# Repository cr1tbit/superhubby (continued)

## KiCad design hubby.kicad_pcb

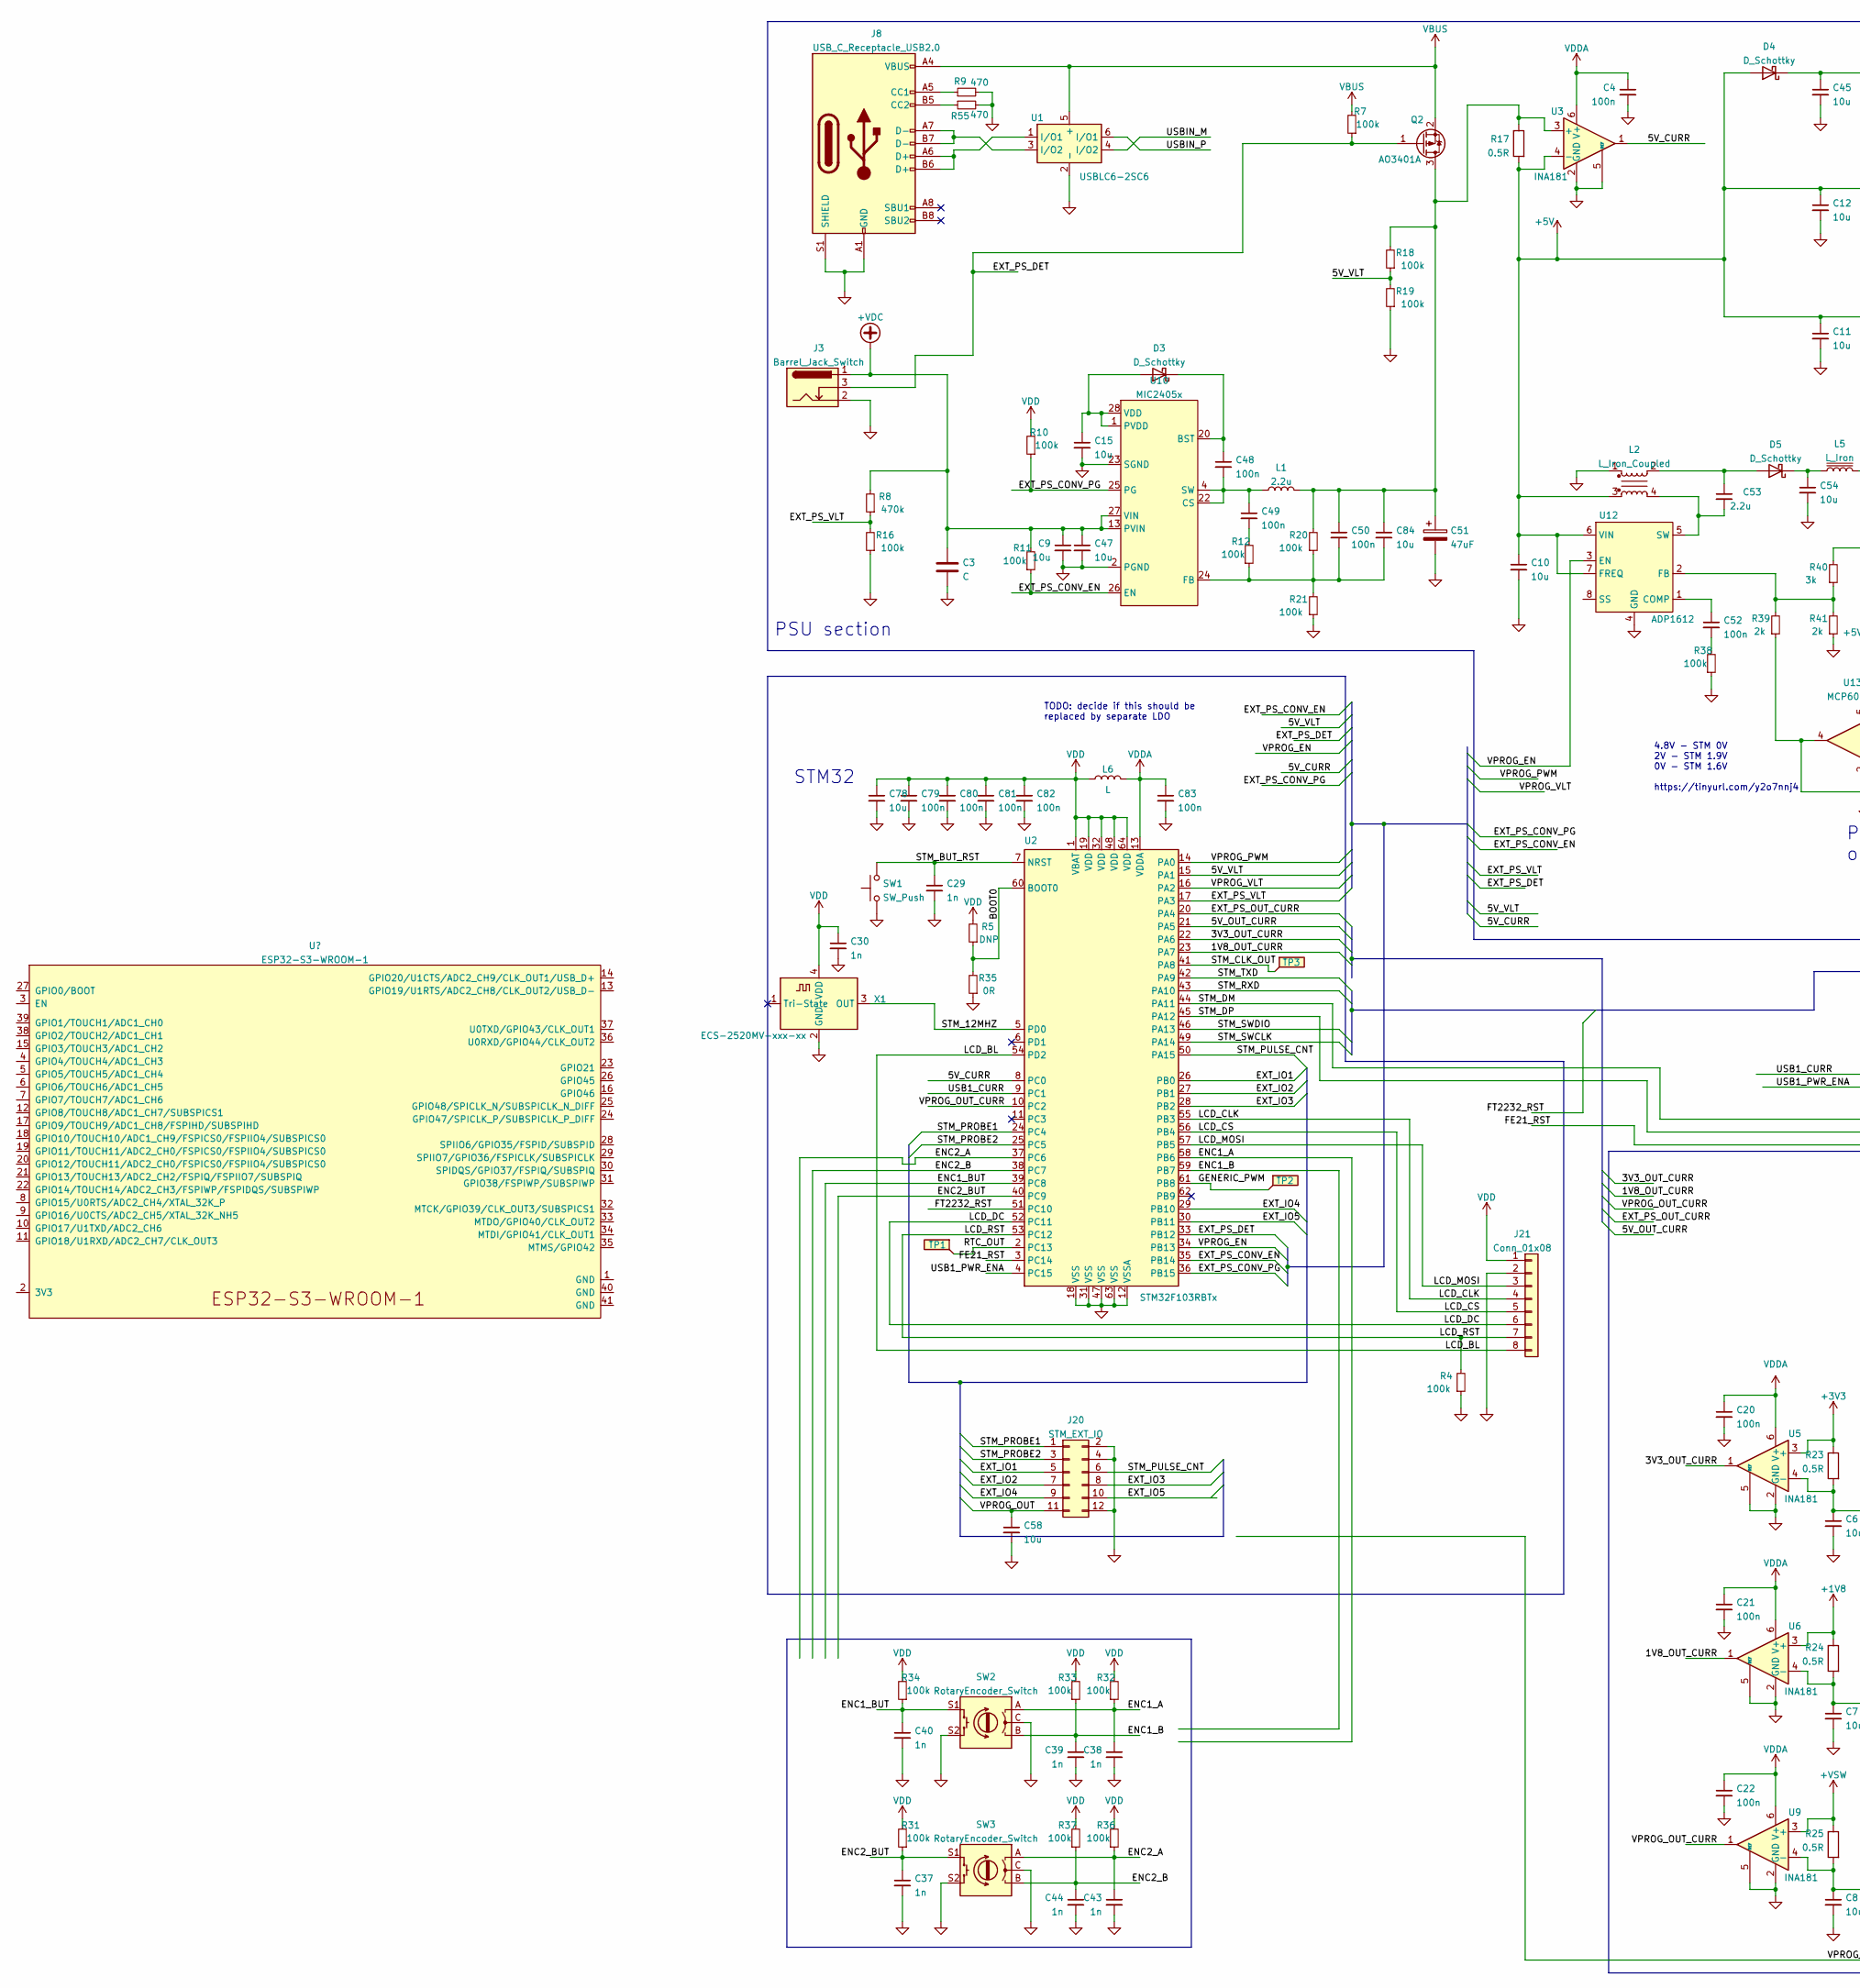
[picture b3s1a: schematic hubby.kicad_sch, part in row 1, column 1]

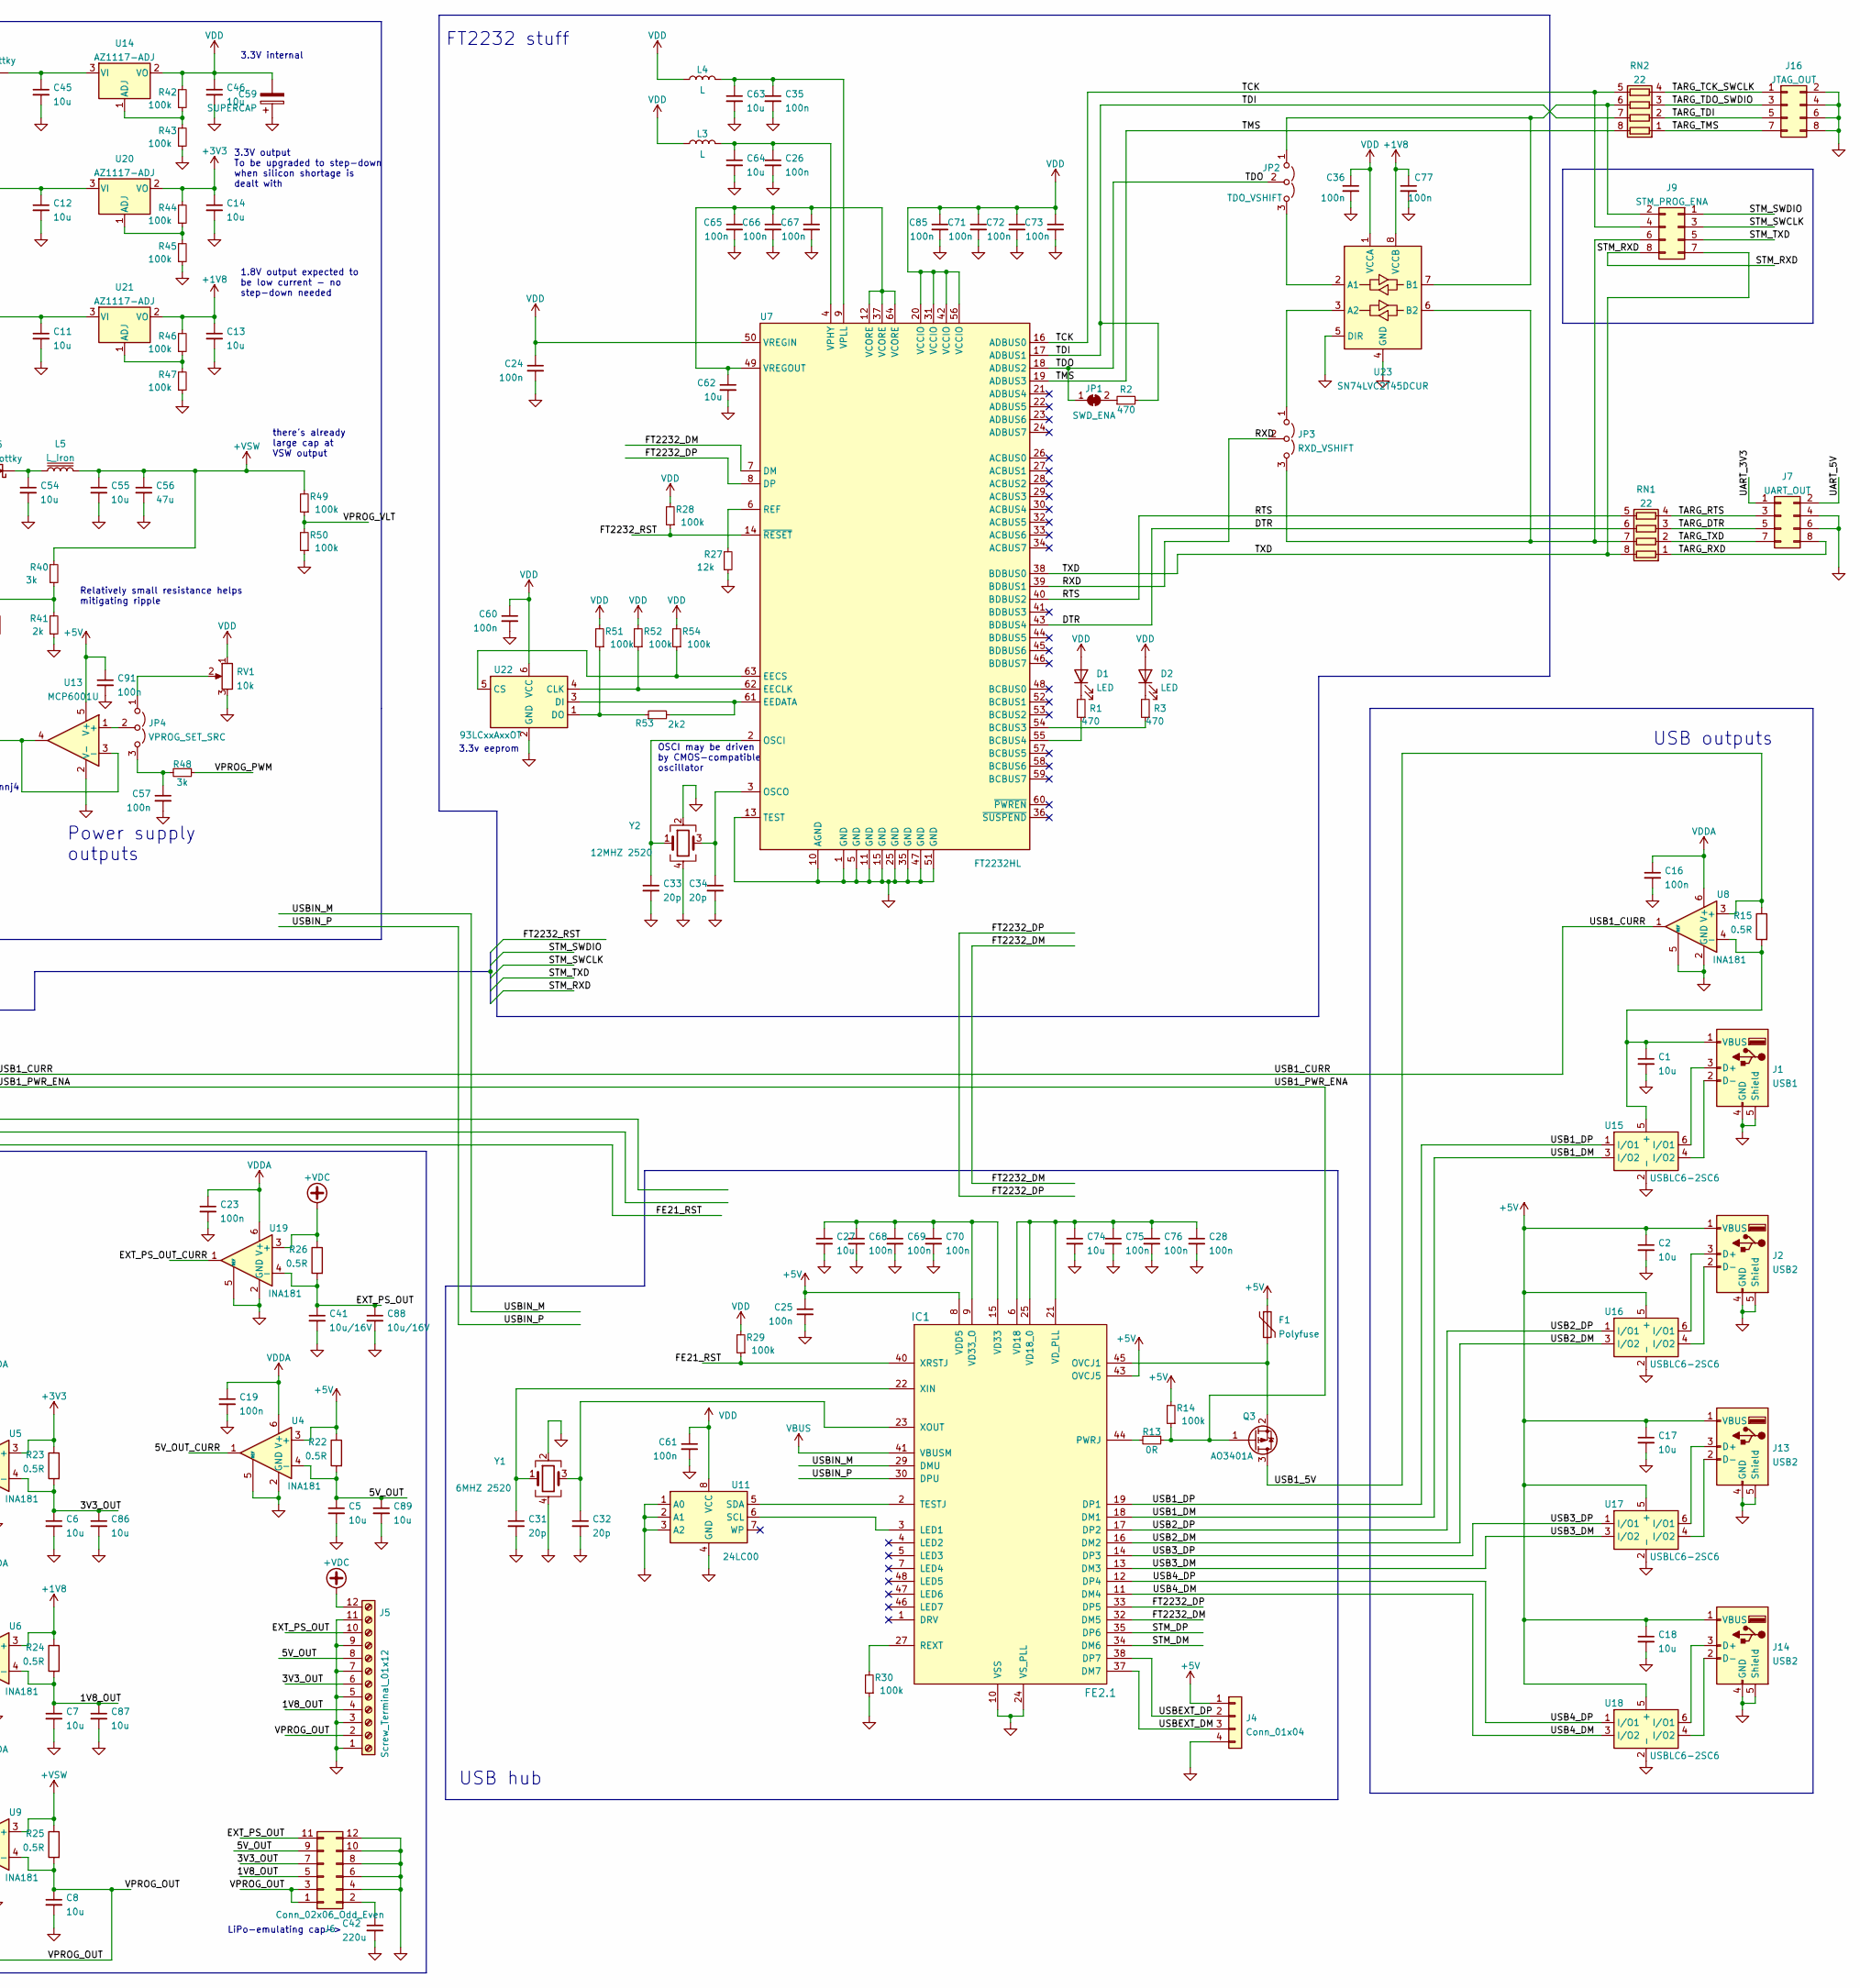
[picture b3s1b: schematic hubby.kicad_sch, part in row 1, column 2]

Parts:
C1, C2, C5, C6, C7, C8, C9, C10, C11, C12, C13, C14, C15, C17, C18, C27, C45, C46, C47, C54, C55, C58, C62, C63, C64, C74, C78, C84, C86, C87, C89: 10u; C_0805_2012Metric
C3: C; CP_Radial_D5.0mm_P2.50mm
C4, C16, C19, C20, C21, C22, C23, C24, C25, C26, C28, C35, C36, C48, C49, C50, C52, C57, C60, C61, C65, C66, C67, C68, C69, C70, C71, C72, C73, C75, C76, C77, C79, C80, C81, C82, C83, C85, C91: 100n; C_0402_1005Metric
C29, C30, C37, C38, C39, C40, C43, C44: 1n; C_0402_1005Metric
C31, C32, C33, C34: 20p; C_0402_1005Metric
C41, C88: 10u/16V; C_0805_2012Metric
C42: 220u; CP_Radial_D5.0mm_P2.50mm
C51: 47uF; CP_Radial_D5.0mm_P2.50mm
C53: 2.2u; C_0805_2012Metric
C56: 47u; C_0805_2012Metric
C59: SUPERCAP; CP_Radial_D5.0mm_P2.50mm
D1, D2: LED; LED_0805_2012Metric_Pad1.15x1.40mm_HandSolder
D3, D4, D5: D_Schottky; D_SMA
F1: Polyfuse; R_1206_3216Metric_Pad1.30x1.75mm_HandSolder
IC1: FE2.1; LQFP-48_7x7mm_P0.5mm
J1: USB1; USB_A_Molex_67643_Horizontal
J2, J13, J14: USB2; USB_A_Molex_67643_Horizontal
J3: Barrel_Jack_Switch; BarrelJack_CUI_PJ-102AH_Horizontal
J4: Conn_01x04; PinHeader_1x04_P2.00mm_Vertical
J5: Screw_Terminal_01x12; TerminalBlock_Phoenix_PT-1,5-12-5.0-H_1x12_P5.00mm_Horizont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
J6: Conn_02x06_Odd_Even; PinHeader_2x06_P2.54mm_Horizontal
J7: UART_OUT; PinHeader_2x04_P2.54mm_Horizontal
J8: USB_C_Receptacle_USB2.0; USB_C_Receptacle_GCT_USB4085
J9: STM_PROG_ENA; PinHeader_2x04_P2.54mm_Vertical
J16: JTAG_OUT; PinHeader_2x04_P2.54mm_Horizontal
J20: STM_EXT_IO; PinHeader_2x06_P2.54mm_Horizontal
J21: Conn_01x08; PinSocket_1x08_P2.54mm_Vertical
JP1: SWD_ENA; SolderJumper-2_P1.3mm_Bridged2Bar_RoundedPad1.0x1.5mm
JP2: TDO_VSHIFT; PinHeader_1x03_P2.54mm_Vertical
JP3: RXD_VSHIFT; PinHeader_1x03_P2.54mm_Vertical
JP4: VPROG_SET_SRC; PinHeader_1x03_P2.54mm_Vertical
L1: 2.2u; L_Vishay_IHLP-4040
L2: L_Iron_Coupled; L_Wuerth_WE-DD-Typ-M-Typ-S
L3, L4, L6: L; L_1206_3216Metric_Pad1.22x1.90mm_HandSolder
L5: L_Iron; L_1206_3216Metric_Pad1.42x1.75mm_HandSolder
Q2, Q3: AO3401A; SOT-23
R1, R2, R3, R9, R55: 470; R_0603_1608Metric_Pad0.98x0.95mm_HandSolder
R4, R7, R10, R11, R12, R14, R16, R18, R19, R20, R21, R28, R29, R30, R31, R32, R33, R34, R36, R37, R38, R42, R43, R44, R45, R46, R47, R49, R50, R51, R52, R54: 100k; R_0603_1608Metric_Pad0.98x0.95mm_HandSolder
R5: DNP; R_0603_1608Metric_Pad0.98x0.95mm_HandSolder
R8: 470k; R_0603_1608Metric_Pad0.98x0.95mm_HandSolder
R13, R35: 0R; R_0603_1608Metric_Pad0.98x0.95mm_HandSolder
R15, R17, R22, R23, R24, R25, R26: 0.5R; R_1206_3216Metric_Pad1.30x1.75mm_HandSolder
R27: 12k; R_0603_1608Metric_Pad0.98x0.95mm_HandSolder
R39, R41: 2k; R_0603_1608Metric_Pad0.98x0.95mm_HandSolder
R40, R48: 3k; R_0603_1608Metric_Pad0.98x0.95mm_HandSolder
R53: 2k2; R_0603_1608Metric_Pad0.98x0.95mm_HandSolder
RN1, RN2: 22; R_Array_Convex_4x0603
RV1: 10k; Potentiometer_Runtron_RM-065_Vertical
SW1: SW_Push; SW_PUSH_6mm_H4.3mm
SW2, SW3: RotaryEncoder_Switch; RotaryEncoder_Alps_EC12E-Switch_Vertical_H20mm_CircularMoun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
TP1: RTC_OUT; TestPoint_Pad_D1.0mm
TP2: GENERIC_PWM; TestPoint_Pad_D1.0mm
TP3: STM_CLK_OUT; TestPoint_Pad_D1.0mm
U1, U15, U16, U17, U18: USBLC6-2SC6; SOT-23-6
U2: STM32F103RBTx; LQFP-64_10x10mm_P0.5mm
U3, U4, U5, U6, U8, U9, U19: INA181; SOT-23-6
U7: FT2232HL; LQFP-64_10x10mm_P0.5mm
U10: MIC2405x; QFN-28-3EP_5x6mm_MIC2045x
U11: 24LC00; SOIC-8_3.9x4.9mm_P1.27mm
U12: ADP1612; MSOP-8_3x3mm_P0.65mm
U13: MCP6001U; SOT-23-5
U14, U20, U21: AZ1117-ADJ; SOT-223-3_TabPin2
U22: 93LCxxAxxOT; SOT-23-6
U23: SN74LVC2T45DCUR; VSSOP-8_2.4x2.1mm_P0.5mm
X1: ECS-2520MV-xxx-xx; Oscillator_SMD_ECS_2520MV-xxx-xx-4Pin_2.5x2.0mm
Y1: 6MHZ 2520; Crystal_SMD_2520-4Pin_2.5x2.0mm
Y2: 12MHZ 2520; Crystal_SMD_2520-4Pin_2.5x2.0mm

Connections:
+1V8: C13.1, C77.1, R24.1, R46.2, U6.3 (+), U21.2 (VO), U23.8 (VCCB)
+3V3: C14.1, R23.1, R44.2, U5.3 (+), U20.2 (VO)
+5V: C2.1, C10.1, C11.1, C12.1, C17.1, C18.1, C25.1, C91.1, D4.2 (A), F1.1, IC1.8 (VDD5), IC1.43 (OVCJ5), J2.1 (VBUS), J4.1, J13.1 (VBUS), J14.1 (VBUS), L2.3, R14.2, R17.2, R22.1, U3.4 (-), U4.3 (+), U12.6 (VIN), U12.7 (FREQ), U13.5 (V+), U16.5 (+), U17.5 (+), U18.5 (+), U20.3 (VI), U21.3 (VI)
+VDC: C3.1, C9.1, C47.1, J3.1, J5.12, R8.2, R11.2, R26.1, U10.13 (PVIN), U10.14 (PVIN), U10.15 (PVIN), U10.16 (PVIN), U10.17 (PVIN), U10.18 (PVIN), U10.19 (PVIN), U10.27 (VIN), U19.3 (+)
+VSW: C55.1, C56.1, L5.2, R25.1, R40.2, R49.2, U9.3 (+)
/1V8_OUT: C7.1, C87.1, J5.4, J6.5, R24.2, U6.4 (-)
/1V8_OUT_CURR: U2.23 (PA7), U6.1
/3V3_OUT: C6.1, C86.1, J5.6, J6.7, R23.2, U5.4 (-)
/3V3_OUT_CURR: U2.22 (PA6), U5.1
/5V_CURR: U2.8 (PC0), U3.1
/5V_OUT: C5.1, C89.1, J5.8, J6.9, R22.2, U4.4 (-)
/5V_OUT_CURR: U2.21 (PA5), U4.1
/5V_VLT: R18.1, R19.2, U2.15 (PA1)
/BOOT0: R5.1, R35.2, U2.60 (BOOT0)
/DTR: RN1.6 (R3.2), U7.43 (BDBUS4)
/ENC1_A: C38.1, R32.1, SW2.A, U2.58 (PB6)
/ENC1_B: C39.1, R33.1, SW2.B, U2.59 (PB7)
/ENC1_BUT: C40.1, R34.1, SW2.S1, U2.39 (PC8)
/ENC2_A: C43.1, R36.1, SW3.A, U2.37 (PC6)
/ENC2_B: C44.1, R37.1, SW3.B, U2.38 (PC7)
/ENC2_BUT: C37.1, R31.1, SW3.S1, U2.40 (PC9)
/EXT_IO1: J20.5, U2.26 (PB0)
/EXT_IO2: J20.7, U2.27 (PB1)
/EXT_IO3: J20.8, U2.28 (PB2)
/EXT_IO4: J20.9, U2.29 (PB10)
/EXT_IO5: J20.10, U2.30 (PB11)
/EXT_PS_CONV_EN: R11.1, U2.35 (PB14), U10.26 (EN)
/EXT_PS_CONV_PG: R10.1, U2.36 (PB15), U10.25 (PG)
/EXT_PS_DET: J3.3, Q2.1 (G), R7.1, U2.33 (PB12)
/EXT_PS_OUT: C41.1, C88.1, J5.10, J6.11, R26.2, U19.4 (-)
/EXT_PS_OUT_CURR: U2.20 (PA4), U19.1
/EXT_PS_VLT: R8.1, R16.2, U2.17 (PA3)
/FE21_RST: IC1.40 (XRSTJ), R29.1, U2.3 (PC14)
/FT2232_DM: IC1.32 (DM5), U7.7 (DM)
/FT2232_DP: IC1.33 (DP5), U7.8 (DP)
/FT2232_RST: R28.1, U2.51 (PC10), U7.14 (~RESET)
/GENERIC_PWM: TP2.1, U2.61 (PB8)
/LCD_BL: J21.8, U2.54 (PD2)
/LCD_CLK: J21.4, U2.55 (PB3)
/LCD_CS: J21.5, U2.56 (PB4)
/LCD_DC: J21.6, U2.52 (PC11)
/LCD_MOSI: J21.3, U2.57 (PB5)
/LCD_RST: J21.7, R4.2, U2.53 (PC12)
/RTC_OUT: TP1.1, U2.2 (PC13)
/RTS: RN1.5 (R4.2), U7.40 (BDBUS2)
/RXD: JP3.2 (C), U7.39 (BDBUS1)
/STM_12MHZ: U2.5 (PD0), X1.3 (OUT)
/STM_BUT_RST: C29.1, SW1.2, U2.7 (NRST)
/STM_CLK_OUT: TP3.1, U2.41 (PA8)
/STM_DM: IC1.34 (DM6), U2.44 (PA11)
/STM_DP: IC1.35 (DP6), U2.45 (PA12)
/STM_PROBE1: J20.1, U2.24 (PC4)
/STM_PROBE2: J20.3, U2.25 (PC5)
/STM_PULSE_CNT: J20.6, U2.50 (PA15)
/STM_RXD: J9.8, U2.43 (PA10)
/STM_SWCLK: J9.3, U2.49 (PA14)
/STM_SWDIO: J9.1, U2.46 (PA13)
/STM_TXD: J9.5, U2.42 (PA9)
/TARG_DTR: J7.5, RN1.3 (R3.1)
/TARG_RTS: J7.3, RN1.4 (R4.1)
/TARG_RXD: J7.8, RN1.1 (R1.1)
/TARG_TCK_SWCLK: J16.1, RN2.4 (R4.1)
/TARG_TDI: J16.5, RN2.2 (R2.1)
/TARG_TDO_SWDIO: J16.3, RN2.3 (R3.1)
/TARG_TMS: J16.7, RN2.1 (R1.1)
/TARG_TXD: J7.7, RN1.2 (R2.1)
/TCK: J9.4, RN2.5 (R4.2), U7.16 (ADBUS0)
/TDI: R2.2, RN2.7 (R2.2), U7.17 (ADBUS1)
/TDO: JP1.1 (A), JP2.2 (C), U7.18 (ADBUS2)
/TMS: RN2.8 (R1.2), U7.19 (ADBUS3)
/TXD: J9.7, RN1.8 (R1.2), U7.38 (BDBUS0)
/UART_3V3: J7.1
/UART_5V: J7.2
/USB1_5V: Q3.3 (D), R15.1, U8.3 (+)
/USB1_CURR: U2.9 (PC1), U8.1
/USB1_DM: IC1.18 (DM1), U15.3 (I/O2)
/USB1_DP: IC1.19 (DP1), U15.1 (I/O1)
/USB1_PWR_ENA: Q3.1 (G), R13.1, R14.1, U2.4 (PC15)
/USB2_DM: IC1.16 (DM2), U16.3 (I/O2)
/USB2_DP: IC1.17 (DP2), U16.1 (I/O1)
/USB3_DM: IC1.13 (DM3), U17.3 (I/O2)
/USB3_DP: IC1.14 (DP3), U17.1 (I/O1)
/USB4_DM: IC1.11 (DM4), U18.3 (I/O2)
/USB4_DP: IC1.12 (DP4), U18.1 (I/O1)
/USBEXT_DM: IC1.37 (DM7), J4.3
/USBEXT_DP: IC1.38 (DP7), J4.2
/USBIN_M: IC1.29 (DMU), U1.4 (I/O2)
/USBIN_P: IC1.30 (DPU), U1.6 (I/O1)
/VPROG_EN: U2.34 (PB13), U12.3 (EN)
/VPROG_OUT: C8.1, C58.1, J5.2, J6.1, J6.3, J20.11, R25.2, U9.4 (-)
/VPROG_OUT_CURR: U2.10 (PC2), U9.1
/VPROG_PWM: R48.1, U2.14 (PA0)
/VPROG_VLT: R49.1, R50.2, U2.16 (PA2)
GND: C1.2, C2.2, C3.2, C4.2, C5.2, C6.2, C7.2, C8.2, C9.2, C10.2, C11.2, C12.2, C13.2, C14.2, C15.2, C16.2, C17.2, C18.2, C19.2, C20.2, C21.2, C22.2, C23.2, C24.2, C25.2, C26.2, C27.2, C28.2, C29.2, C30.2, C31.2, C32.2, C33.2, C34.2, C35.2, C36.2, C37.2, C38.2, C39.2, C40.2, C41.2, C42.2, C43.2, C44.2, C45.2, C46.2, C47.2, C51.2, C54.2, C55.2, C56.2, C57.2, C58.2, C59.1, C60.2, C61.2, C62.2, C63.2, C64.2, C65.2, C66.2, C67.2, C68.2, C69.2, C70.2, C71.2, C72.2, C73.2, C74.2, C75.2, C76.2, C77.2, C78.2, C79.2, C80.2, C81.2, C82.2, C83.2, C85.2, C86.2, C87.2, C88.2, C89.2, C91.2, IC1.10 (VSS), IC1.24 (VS_PLL), IC1.39 (VSS), J1.4 (GND), J1.5 (Shield), J2.4 (GND), J2.5 (Shield), J3.2, J4.4, J5.1, J5.3, J5.5, J5.7, J5.9, J5.11, J6.4, J6.6, J6.8, J6.10, J6.12, J7.4, J7.6, J8.A1 (GND), J8.A12 (GND), J8.B1 (GND), J8.B12 (GND), J8.S1 (SHIELD), J13.4 (GND), J13.5 (Shield), J14.4 (GND), J14.5 (Shield), J16.2, J16.4, J16.6, J16.8, J20.2, J20.4, J20.12, J21.2, L2.1, R4.1, R9.2, R16.1, R19.1, R21.1, R27.1, R30.1, R35.1, R38.1, R41.1, R43.1, R45.1, R47.1, R50.1, R55.2, RV1.3, SW1.1, SW2.C, SW2.S2, SW3.C, SW3.S2, U1.2 (-), U2.12 (VSSA), U2.18 (VSS), U2.31 (VSS), U2.47 (VSS), U2.63 (VSS), U3.2 (GND), U3.5 (REF), U4.2 (GND), U4.5 (REF), U5.2 (GND), U5.5 (REF), U6.2 (GND), U6.5 (REF), U7.1 (GND), U7.5 (GND), U7.10 (AGND), U7.11 (GND), U7.13 (TEST), U7.15 (GND), U7.25 (GND), U7.35 (GND), U7.47 (GND), U7.51 (GND), U8.2 (GND), U8.5 (REF), U9.2 (GND), U9.5 (REF), U10.2 (PGND), U10.5 (PGND), U10.6 (PGND), U10.7 (PGND), U10.8 (PGND), U10.21 (PGND), U10.23 (SGND), U11.1 (A0), U11.2 (A1), U11.3 (A2), U11.4 (GND), U12.4 (GND), U13.2 (V-), U15.2 (-), U16.2 (-), U17.2 (-), U18.2 (-), U19.2 (GND), U19.5 (REF), U22.2 (GND), U23.4 (GND), U23.5 (DIR), X1.2 (GND), Y1.2, Y1.4, Y2.2, Y2.4
unnamed: C1.1, J1.1 (VBUS), R15.2, U8.4 (-), U15.5 (+)
unnamed: C15.1, D3.2 (A), U10.1 (PVDD), U10.28 (VDD)
unnamed: C26.1, C64.1, L3.2, U7.4 (VPHY)
unnamed: C27.1, C68.1, C69.1, C70.1, IC1.9 (VD33_O), IC1.15 (VD33), IC1.20 (VD33), IC1.26 (VD33), IC1.31 (VD33), IC1.36 (VD33), IC1.42 (VD33)
unnamed: C28.1, C74.1, C75.1, C76.1, IC1.6 (VD18), IC1.21 (VD_PLL), IC1.25 (VD18_0), IC1.28 (VD18)
unnamed: C31.1, IC1.22 (XIN), Y1.1
unnamed: C32.1, IC1.23 (XOUT), Y1.3
unnamed: C33.1, U7.2 (OSCI), Y2.1
unnamed: C34.1, U7.3 (OSCO), Y2.3
unnamed: C35.1, C63.1, L4.2, U7.9 (VPLL)
unnamed: C42.1, J6.2
unnamed: C45.1, D4.1 (K), U14.3 (VI)
unnamed: C48.1, D3.1 (K), U10.20 (BST)
unnamed: C48.2, C49.1, L1.1, U10.4 (SW), U10.9 (SW), U10.10 (SW), U10.11 (SW), U10.12 (SW), U10.22 (CS)
unnamed: C49.2, R12.2
unnamed: C50.1, C51.1, C84.1, L1.2, Q2.3 (D), R17.1, R18.2, R20.2, U3.3 (+)
unnamed: C50.2, C84.2, R12.1, R20.1, R21.2, U10.24 (FB)
unnamed: C52.1, U12.1 (COMP)
unnamed: C52.2, R38.2
unnamed: C53.1, D5.2 (A), L2.2
unnamed: C53.2, L2.4, U12.5 (SW)
unnamed: C54.1, D5.1 (K), L5.1
unnamed: C57.1, JP4.3 (B), R48.2
unnamed: C62.1, C65.1, C66.1, C67.1, U7.12 (VCORE), U7.37 (VCORE), U7.49 (VREGOUT), U7.64 (VCORE)
unnamed: D1.1 (K), R1.2
unnamed: D2.1 (K), R3.2
unnamed: F1.2, IC1.45 (OVCJ1), Q3.2 (S)
unnamed: IC1.2 (TESTJ), U11.5 (SDA)
unnamed: IC1.3 (LED1), U11.6 (SCL)
unnamed: IC1.27 (REXT), R30.2
unnamed: IC1.44 (PWRJ), R13.2
unnamed: J1.2 (D-), U15.4 (I/O2)
unnamed: J1.3 (D+), U15.6 (I/O1)
unnamed: J2.2 (D-), U16.4 (I/O2)
unnamed: J2.3 (D+), U16.6 (I/O1)
unnamed: J8.A5 (CC1), R9.1
unnamed: J8.A6 (D+), J8.B6 (D+), U1.1 (I/O1)
unnamed: J8.A7 (D-), J8.B7 (D-), U1.3 (I/O2)
unnamed: J8.B5 (CC2), R55.1
unnamed: J9.2, JP2.1 (A), RN2.6 (R3.2), U23.7 (B1)
unnamed: J9.6, JP3.3 (B), RN1.7 (R2.2), U23.6 (B2)
unnamed: J13.2 (D-), U17.4 (I/O2)
unnamed: J13.3 (D+), U17.6 (I/O1)
unnamed: J14.2 (D-), U18.4 (I/O2)
unnamed: J14.3 (D+), U18.6 (I/O1)
unnamed: JP1.2 (B), R2.1
unnamed: JP2.3 (B), U23.2 (A1)
unnamed: JP3.1 (A), U23.3 (A2)
unnamed: JP4.1 (A), RV1.2
unnamed: JP4.2 (C), U13.1 (+)
unnamed: R27.2, U7.6 (REF)
unnamed: R39.1, U13.3 (-), U13.4
unnamed: R39.2, R40.1, R41.2, U12.2 (FB)
unnamed: R42.1, R43.2, U14.1 (ADJ)
unnamed: R44.1, R45.2, U20.1 (ADJ)
unnamed: R46.1, R47.2, U21.1 (ADJ)
unnamed: R51.1, R53.1, U22.1 (DO)
unnamed: R52.1, U7.62 (EECLK), U22.4 (CLK)
unnamed: R53.2, U7.61 (EEDATA), U22.3 (DI)
unnamed: R54.1, U7.63 (EECS), U22.5 (CS)
unnamed: R3.1, U7.54 (BCBUS3)
unnamed: R1.1, U7.55 (BCBUS4)
VBUS: IC1.41 (VBUSM), J8.A4 (VBUS), J8.A9 (VBUS), J8.B4 (VBUS), J8.B9 (VBUS), Q2.2 (S), R7.2, U1.5 (+)
VDD: C24.1, C30.1, C36.1, C46.1, C59.2, C60.1, C61.1, C71.1, C72.1, C73.1, C78.1, C79.1, C80.1, C81.1, C82.1, C85.1, D1.2 (A), D2.2 (A), J21.1, L3.1, L4.1, L6.1, R5.2, R10.2, R28.2, R29.2, R31.2, R32.2, R33.2, R34.2, R36.2, R37.2, R42.2, R51.2, R52.2, R54.2, RV1.1, U2.1 (VBAT), U2.19 (VDD), U2.32 (VDD), U2.48 (VDD), U2.64 (VDD), U7.20 (VCCIO), U7.31 (VCCIO), U7.42 (VCCIO), U7.50 (VREGIN), U7.56 (VCCIO), U11.8 (VCC), U14.2 (VO), U22.6 (VCC), U23.1 (VCCA), X1.4 (VDD)

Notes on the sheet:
USB hub
PSU section
Relatively small resistance helps mitigating ripple
3.3V output To be upgraded to step-down when silicon shortage is dealt with
STM32
USB outputs
there's already large cap at VSW output
3.3V internal
4.8V - STM 0V 2V - STM 1.9V 0V - STM 1.6V https://tinyurl.com/y2o7nnj4
Power supply outputs
1.8V output expected to be low current - no step-down needed
3.3v eeprom
LiPo-emulating cap->
TODO: decide if this should be replaced by separate LDO
FT2232 stuff
OSCI may be driven by CMOS-compatible oscillator

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
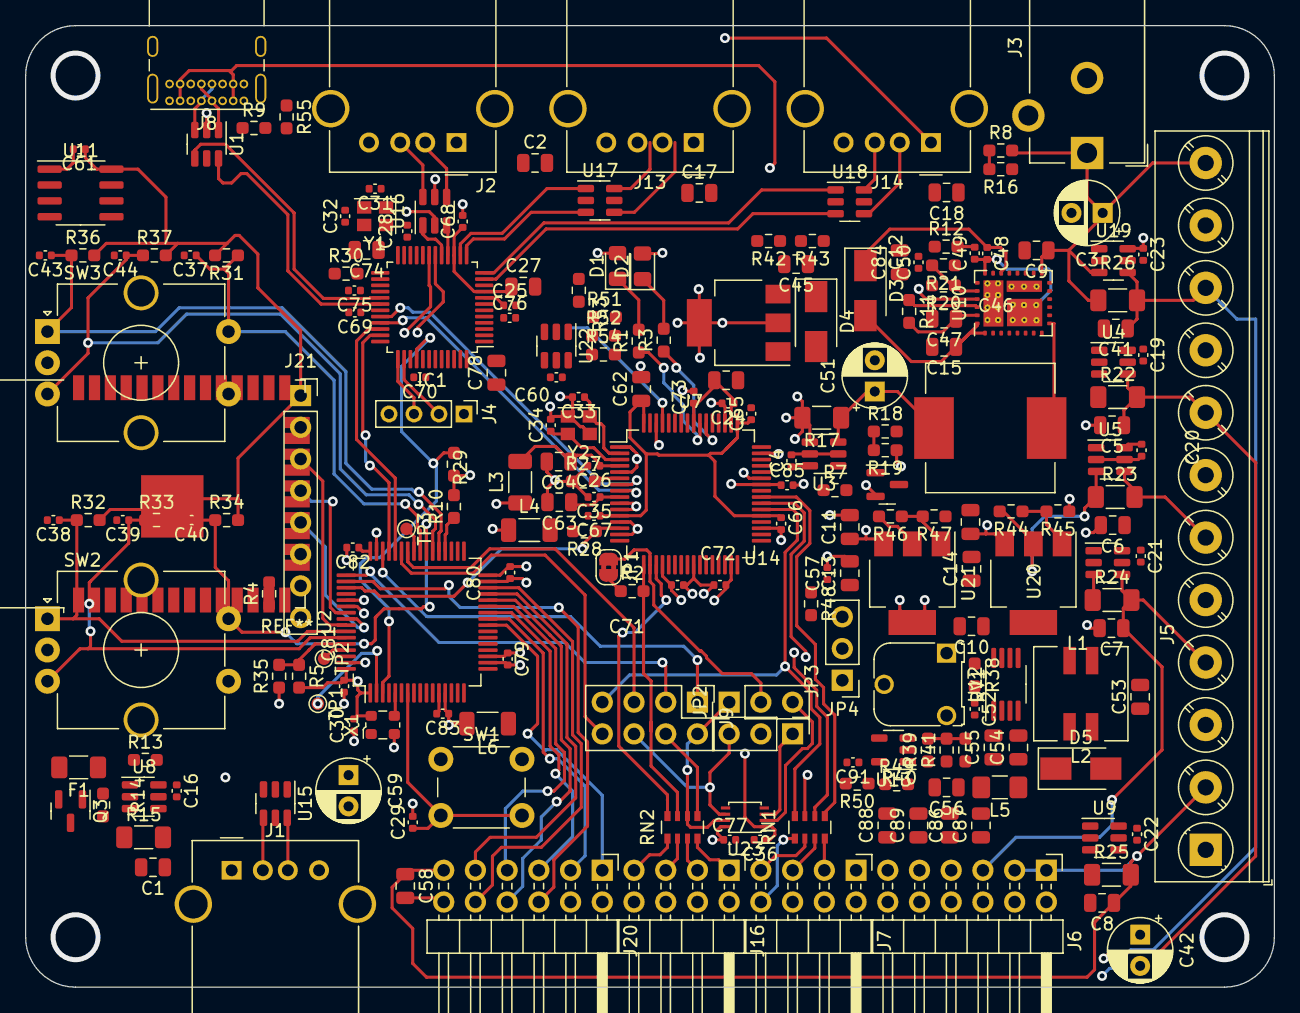
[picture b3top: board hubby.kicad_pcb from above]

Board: 4 copper layers, 100.0 x 77.0 mm, 212 parts (0 on the bottom side), 157 nets.

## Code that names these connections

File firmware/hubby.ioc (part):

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Mcu.Name=STM32F103R(F-G)Tx
Mcu.Package=LQFP64
Mcu.UserName=STM32F103RFTx
PA0-WKUP.GPIOParameters=GPIO_Label
PA0-WKUP.GPIO_Label=VPROG_PWM
PA0-WKUP.Signal=S_TIM5_CH1
PA1.GPIOParameters=GPIO_Label
PA1.GPIO_Label=_5V_VLT
PA1.Signal=ADCx_IN1
PA10.GPIOParameters=GPIO_Label
PA10.GPIO_Label=STM_RXD
PA10.Mode=Asynchronous
PA10.Signal=USART1_RX
PA11.GPIOParameters=GPIO_Label
PA11.GPIO_Label=STM_DM
PA11.Mode=Device
PA11.Signal=USB_DM
PA12.GPIOParameters=GPIO_Label
PA12.GPIO_Label=STM_DP
PA12.Mode=Device
PA12.Signal=USB_DP
PA13.GPIOParameters=GPIO_Label
PA13.GPIO_Label=STM_SWDIO
PA13.Mode=Serial_Wire
PA13.Signal=SYS_JTMS-SWDIO
PA14.GPIOParameters=GPIO_Label
PA14.GPIO_Label=STM_SWCLK
PA14.Mode=Serial_Wire
PA14.Signal=SYS_JTCK-SWCLK
PA15.GPIOParameters=GPIO_Label
PA15.GPIO_Label=STM_PULSE_CNT
PA15.Signal=S_TIM2_CH1_ETR
PA2.GPIOParameters=GPIO_Label
PA2.GPIO_Label=VPROG_VLT
PA2.Signal=ADCx_IN2
PA3.GPIOParameters=GPIO_Label
PA3.GPIO_Label=EXT_PS_VLT
PA3.Signal=ADCx_IN3
PA4.GPIOParameters=GPIO_Label
PA4.GPIO_Label=EXT_PS_OUT_CURR
PA4.Signal=ADCx_IN4
PA5.GPIOParameters=GPIO_Label
PA5.GPIO_Label=_5V_OUT_CURR
PA5.Signal=ADCx_IN5
PA6.GPIOParameters=GPIO_Label
PA6.GPIO_Label=_3V3_OUT_CURR
PA6.Signal=ADCx_IN6
PA7.GPIOParameters=GPIO_Label
PA7.GPIO_Label=_1V8_OUT_CURR
PA7.Signal=ADCx_IN7
PA8.GPIOParameters=GPIO_Label
PA8.GPIO_Label=STM_CLK_OUT
PA8.Mode=Clock-out
PA8.Signal=RCC_MCO
PA9.GPIOParameters=GPIO_Label
PA9.GPIO_Label=STM_TXD
PA9.Mode=Asynchronous
PA9.Signal=USART1_TX
PB0.GPIOParameters=GPIO_Label
PB0.GPIO_Label=EXT_IO1
PB0.Signal=GPIO_Input
PB1.GPIOParameters=GPIO_Label
PB1.GPIO_Label=EXT_IO2
PB1.Signal=GPIO_Input
PB10.GPIOParameters=GPIO_Label
PB10.GPIO_Label=EXT_IO4
PB10.Signal=GPIO_Input
PB11.GPIOParameters=GPIO_Label
PB11.GPIO_Label=EXT_IO5
PB11.Signal=GPIO_Input
PB12.GPIOParameters=GPIO_Label
PB12.GPIO_Label=EXT_PS_DET
PB12.Signal=GPIO_Input
PB13.GPIOParameters=GPIO_Label
PB13.GPIO_Label=VPROG_EN
PB13.Signal=GPIO_Output
PB14.GPIOParameters=GPIO_Label
PB14.GPIO_Label=EXT_PS_CONV_EN
PB14.Signal=GPIO_Output
PB15.GPIOParameters=GPIO_Label
PB15.GPIO_Label=EXT_PS_CONV_PG
PB15.Signal=GPIO_Input
PB2.GPIOParameters=GPIO_Label
PB2.GPIO_Label=EXT_IO3
PB2.Signal=GPIO_Input
PB3.GPIOParameters=GPIO_Label
PB3.GPIO_Label=LCD_CLK
PB3.Mode=TX_Only_Simplex_Unidirect_Master
PB3.Signal=SPI1_SCK
PB4.GPIOParameters=GPIO_Label
PB4.GPIO_Label=LCD_CS
PB4.Signal=GPIO_Output
PB5.GPIOParameters=GPIO_Label
PB5.GPIO_Label=LCD_MOSI
PB5.Mode=TX_Only_Simplex_Unidirect_Master
PB5.Signal=SPI1_MOSI
PB6.GPIOParameters=GPIO_Label
PB6.GPIO_Label=ENC1_A
PB6.Signal=S_TIM4_CH1
PB7.GPIOParameters=GPIO_Label
PB7.GPIO_Label=ENC1_B
PB7.Signal=S_TIM4_CH2
PB8.GPIOParameters=GPIO_Label
PB8.GPIO_Label=GENERIC_PWM
PB8.Signal=S_TIM10_CH1
PC0.GPIOParameters=GPIO_Label
PC0.GPIO_Label=_5V_CURR
PC0.Signal=ADCx_IN10
PC1.GPIOParameters=GPIO_Label
PC1.GPIO_Label=USB1_CURR
PC1.Signal=ADCx_IN11
PC10.GPIOParameters=GPIO_Label
PC10.GPIO_Label=FT2232_RST
PC10.Signal=GPIO_Output
PC11.GPIOParameters=GPIO_Label
PC11.GPIO_Label=LCD_DC
PC11.Signal=GPIO_Output
PC12.GPIOParameters=GPIO_Label
PC12.GPIO_Label=LCD_RST
PC12.Signal=GPIO_Output
PC13-TAMPER-RTC.Mode=RTC OUT
PC13-TAMPER-RTC.Signal=RTC_OUT
PC14-OSC32_IN.GPIOParameters=GPIO_Label
PC14-OSC32_IN.GPIO_Label=FE21_RST
PC14-OSC32_IN.Signal=GPIO_Output
PC15-OSC32_OUT.GPIOParameters=GPIO_Label
PC15-OSC32_OUT.GPIO_Label=USB1_PWR_ENA
PC15-OSC32_OUT.Signal=GPIO_Output
PC2.GPIOParameters=GPIO_Label
PC2.GPIO_Label=VPROG_OUT_CURR
PC2.Signal=ADCx_IN12
PC3.GPIOParameters=GPIO_Label
PC3.GPIO_Label=_5V_VLT
PC3.Signal=ADCx_IN13
PC4.Signal=ADCx_IN14
PC5.GPIOParameters=GPIO_Label
PC5.GPIO_Label=STM_PROBE2
PC5.Signal=ADCx_IN15
PC6.GPIOParameters=GPIO_Label
PC6.GPIO_Label=ENC2_B
PC6.Signal=S_TIM8_CH1
PC7.GPIOParameters=GPIO_Label
PC7.GPIO_Label=ENC2_A
PC7.Signal=S_TIM8_CH2
PC8.GPIOParameters=GPIO_Label
PC8.GPIO_Label=ENC1_BUT
PC8.Signal=GPIO_Input
PC9.GPIOParameters=GPIO_Label
PC9.GPIO_Label=ENC2_BUT
PC9.Signal=GPIO_Input
PD0-OSC_IN.Mode=HSE-External-Clock-Source
PD0-OSC_IN.Signal=RCC_OSC_IN
PD1-OSC_OUT.Mode=HSE-External-Clock-Source
PD1-OSC_OUT.Signal=RCC_OSC_OUT
PD2.GPIOParameters=GPIO_Label
PD2.GPIO_Label=LCD_BL
PD2.Signal=GPIO_Output
RCC.HSE_VALUE=12000000
RCC.SYSCLKFreq_VALUE=72000000
RCC.SYSCLKSource=RCC_SYSCLKSOURCE_PLLCLK
board=custom

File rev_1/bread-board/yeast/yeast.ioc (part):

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Mcu.Name=STM32F103R(F-G)Tx
Mcu.Package=LQFP64
Mcu.UserName=STM32F103RFTx
PA0-WKUP.Signal=ADCx_IN0
PA1.Signal=ADCx_IN1
PA10.Mode=Asynchronous
PA10.Signal=USART1_RX
PA11.Mode=Device
PA11.Signal=USB_DM
PA12.Mode=Device
PA12.Signal=USB_DP
PA13.Mode=Serial_Wire
PA13.Signal=SYS_JTMS-SWDIO
PA14.Mode=Serial_Wire
PA14.Signal=SYS_JTCK-SWCLK
PA15.GPIOParameters=GPIO_Label
PA15.GPIO_Label=PSU_PWM
PA15.Signal=S_TIM2_CH1_ETR
PA2.Signal=ADCx_IN2
PA3.Signal=ADCx_IN3
PA4.Signal=ADCx_IN4
PA5.Signal=ADCx_IN5
PA6.Signal=ADCx_IN6
PA7.Signal=ADCx_IN7
PA8.GPIOParameters=GPIO_Label
PA8.GPIO_Label=FE21_RST
PA8.Signal=GPIO_Output
PA9.Mode=Asynchronous
PA9.Signal=USART1_TX
PB0.Signal=ADCx_IN8
PB1.Signal=ADCx_IN9
PB10.GPIOParameters=GPIO_Label
PB10.GPIO_Label=LOADSW_USB3
PB10.Signal=GPIO_Output
PB11.GPIOParameters=GPIO_Label
PB11.GPIO_Label=LOADSW_USB4
PB11.Signal=GPIO_Output
PB12.Mode=NSS_Signal_Hard_Input
PB12.Signal=SPI2_NSS
PB13.Mode=Full_Duplex_Slave
PB13.Signal=SPI2_SCK
PB14.Mode=Full_Duplex_Slave
PB14.Signal=SPI2_MISO
PB15.Mode=Full_Duplex_Slave
PB15.Signal=SPI2_MOSI
PB2.GPIOParameters=GPIO_Label
PB2.GPIO_Label=LOADSW_USB2
PB2.Signal=GPIO_Output
PB6.Mode=I2C
PB6.Signal=I2C1_SCL
PB7.Mode=I2C
PB7.Signal=I2C1_SDA
PB9.GPIOParameters=GPIO_Label
PB9.GPIO_Label=VPROG_EN
PB9.Signal=GPIO_Output
PC0.Signal=ADCx_IN10
PC1.Signal=ADCx_IN11
PC10.GPIOParameters=GPIO_Label
PC10.GPIO_Label=LOADSW_USB1
PC10.Signal=GPIO_Output
PC13-TAMPER-RTC.GPIOParameters=GPIO_Label
PC13-TAMPER-RTC.GPIO_Label=USBIN_SEL
PC13-TAMPER-RTC.Signal=GPIO_Output
PC14-OSC32_IN.GPIOParameters=GPIO_Label
PC14-OSC32_IN.GPIO_Label=EXT_PS_CONV_EN
PC14-OSC32_IN.Signal=GPIO_Output
PC15-OSC32_OUT.GPIOParameters=GPIO_Label
PC15-OSC32_OUT.GPIO_Label=EXT_PS_CONV_PG
PC15-OSC32_OUT.Signal=GPIO_Input
PC2.Signal=ADCx_IN12
PC3.Signal=ADCx_IN13
PC4.Signal=ADCx_IN14
PC5.Signal=ADCx_IN15
PC6.GPIOParameters=GPIO_Label
PC6.GPIO_Label=CON_GPIO1
PC6.Signal=GPIO_Input
PC7.GPIOParameters=GPIO_Label
PC7.GPIO_Label=CON_GPIO2
PC7.Signal=GPIO_Input
PC8.GPIOParameters=GPIO_Label
PC8.GPIO_Label=CON_GPIO3
PC8.Signal=GPIO_Input
PC9.GPIOParameters=GPIO_Label
PC9.GPIO_Label=CON_GPIO4
PC9.Signal=GPIO_Input
PD0-OSC_IN.Mode=HSE-External-Oscillator
PD0-OSC_IN.Signal=RCC_OSC_IN
PD1-OSC_OUT.Mode=HSE-External-Oscillator
PD1-OSC_OUT.Signal=RCC_OSC_OUT
RCC.HSE_VALUE=6000000
RCC.SYSCLKFreq_VALUE=48000000
RCC.SYSCLKSource=RCC_SYSCLKSOURCE_PLLCLK
board=custom

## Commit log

2021-12-06 1st commit
2021-12-12 commiting cause i'm terrified of kicad 5.99
2021-12-15 another progress checkpoint
2022-02-19 commiting before swapping MCUs
2022-04-08 commiting changes before large concept change
2022-04-10 splitting the board into a literal sandvich
2022-04-15 moving to new pc
2022-05-12 checkpoint before yet another project structure change
2022-05-21 adding yeast^WcubeMX project, working on pcb
2022-05-22 adding some goodies to shcematic
2022-05-25 I forgor 💀
2022-05-26 routing AAAAAAAAAAAAAAA
2022-08-08 WIP commit
2022-09-17 another schematic refactor smh
2022-09-20 more schematic refactor, minor STM gpio changes
